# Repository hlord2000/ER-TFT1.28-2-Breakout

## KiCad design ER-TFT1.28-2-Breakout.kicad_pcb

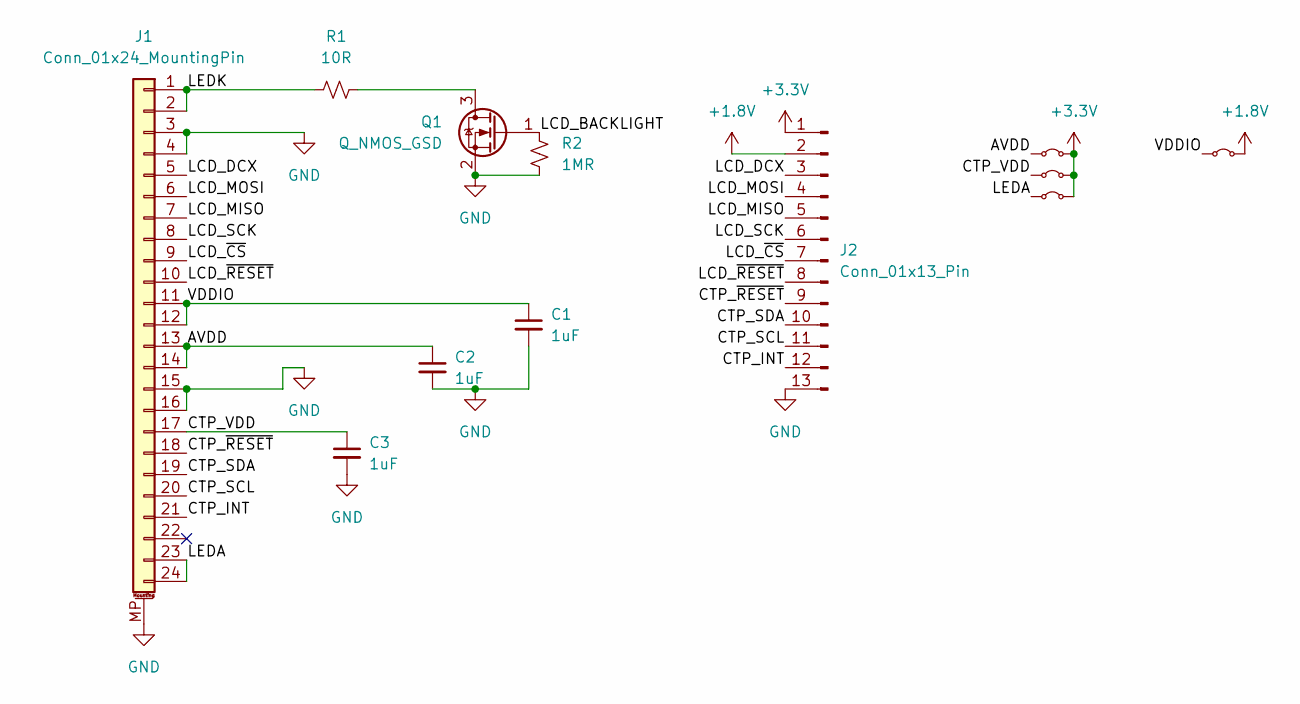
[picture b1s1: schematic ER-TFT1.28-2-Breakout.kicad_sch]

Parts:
C1, C2, C3: 1uF; C_0402_1005Metric
J1: Conn_01x24_MountingPin; YXT-BB10-24S-02; LCSC C2763965
J2: Conn_01x13_Pin; PinSocket_1x13_P2.54mm_Vertical
JP1, JP2, JP3, JP4: Jumper_2_Small_Bridged; SolderJumper-2_P1.3mm_Bridged_Pad1.0x1.5mm
Q1: Q_NMOS_GSD; SOT-23
R1: 10R; R_0603_1608Metric
R2: 1MR; R_0402_1005Metric

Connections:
+1.8V: J2.2, JP4.2 (B)
+3.3V: J2.1, JP1.2 (B), JP2.2 (B), JP3.2 (B)
/AVDD: C2.1, J1.13, J1.14, JP1.1 (A)
/CTP_INT: J1.21, J2.12
/CTP_SCL: J1.20, J2.11
/CTP_SDA: J1.19, J2.10
/CTP_VDD: C3.1, J1.17, JP2.1 (A)
/CTP_~RESET: J1.18, J2.9
/LCD_BACKLIGHT: Q1.1 (G), R2.1
/LCD_DCX: J1.5, J2.3
/LCD_MISO: J1.7, J2.5
/LCD_MOSI: J1.6, J2.4
/LCD_SCK: J1.8, J2.6
/LCD_~CS: J1.9, J2.7
/LCD_~RESET: J1.10, J2.8
/LEDA: J1.23, J1.24, JP3.1 (A)
/LEDK: J1.1, J1.2, R1.1
/VDDIO: C1.1, J1.11, J1.12, JP4.1 (A)
GND: C1.2, C2.2, C3.2, J1.3, J1.4, J1.15, J1.16, J1.MP (MountPin), J2.13, Q1.2 (S), R2.2
unnamed: Q1.3 (D), R1.2

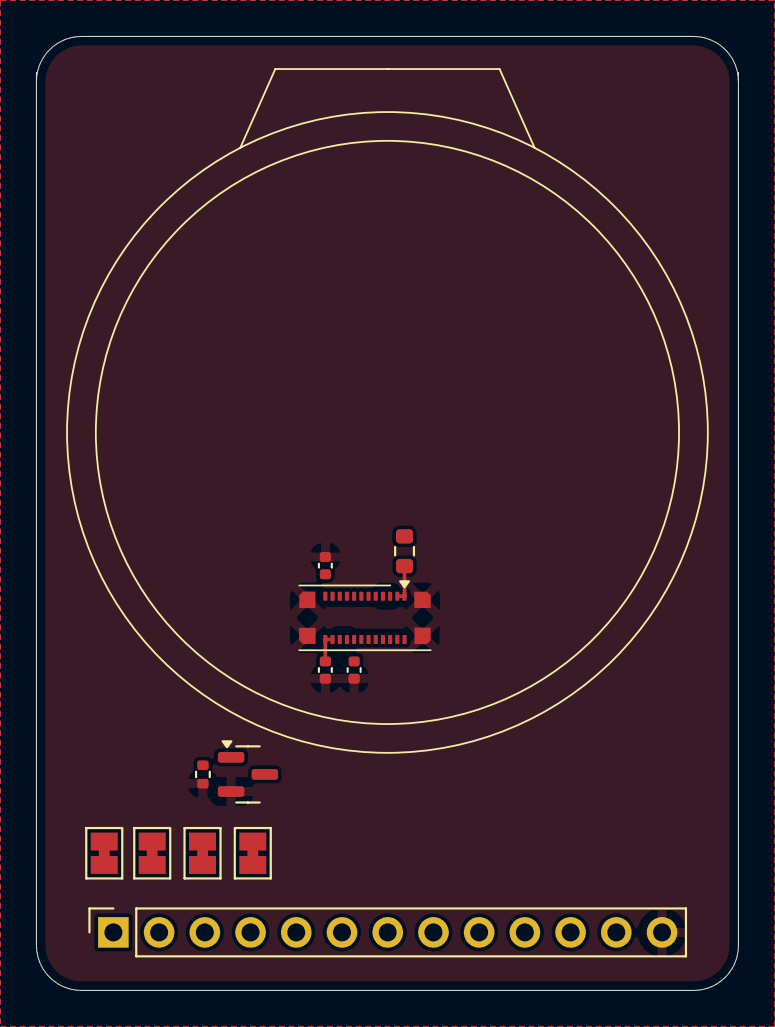
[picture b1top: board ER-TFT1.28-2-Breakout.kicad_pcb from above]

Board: 2 copper layers, 39.0 x 53.0 mm, 12 parts (0 on the bottom side), 20 nets.

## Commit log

2024-10-23 Initial commit.
